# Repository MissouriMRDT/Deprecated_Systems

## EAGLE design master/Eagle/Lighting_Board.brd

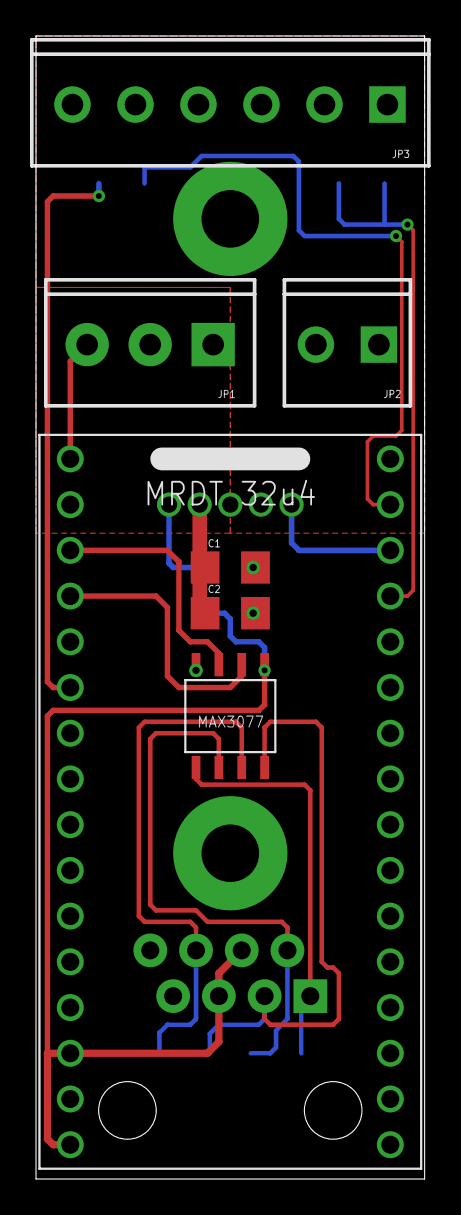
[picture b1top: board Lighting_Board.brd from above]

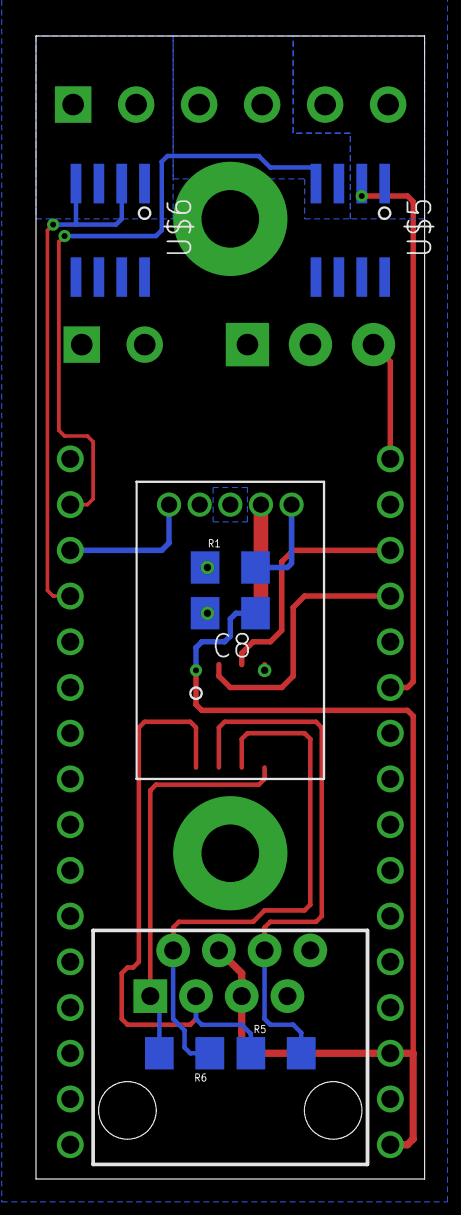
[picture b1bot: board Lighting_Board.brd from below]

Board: 2 copper layers, 21.6 x 63.5 mm, 17 parts (8 on the bottom side), 19 nets.

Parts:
C1, C2: 1206
C8: 1uF; C1206
JP1: SCREWTERMINAL-3.5MM-3
JP2: M023.5MM; SCREWTERMINAL-3.5MM-2
JP3: SCREWTERMINAL-3.5MM-6
R1: 268; 1206
R5, R6: 120 Ohm; 1206
S1, S2: STANDOFF_ELECTRICAL; STANDOFF-ELECTRICAL
U$1: OKR-T/10-W12-C
U$2: 32U4_BREAKOUT; 32U4_MCU_DIP
U$3: MAX3077; MAX3070E
U$4: RJ45-8PTH; RJ45-8
U$5, U$6: IRF8910; SO8

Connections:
+5V: C8.1, U$2.14, U$2.16, U$3.VCC, U$4.4, U$4.5
D4: JP1.3, U$2.1
D8: U$1.P$5, U$2.30
G1: U$2.6, U$5.2
G2: U$2.31, U$5.4
G3: U$2.29, U$6.2, U$6.4
GND: C1.2, C2.2, C8.2, JP1.1, JP2.1, R1.1, S1.P1, S2.P1, U$1.P$3, U$2.15, U$2.17, U$3.GND, U$4.7, U$4.8, U$5.5, U$5.6, U$5.7, U$5.8, U$6.5, U$6.6, U$6.7, U$6.8
unnamed: R1.2, U$1.P$1
unnamed: R6.2, U$3.Y, U$4.1
unnamed: R6.1, U$3.Z, U$4.2
unnamed: R5.2, U$3.B, U$4.6
unnamed: R5.1, U$3.A, U$4.3
unnamed: U$2.3, U$3.DI
RXD: U$2.4, U$3.RO
S1: JP3.5, U$5.1
S2: JP3.3, U$5.3
S3: JP3.1, U$6.1, U$6.3
VDD: C1.1, C2.1, JP1.2, U$1.P$2
VIN: JP2.2, JP3.2, JP3.4, JP3.6, U$1.P$4

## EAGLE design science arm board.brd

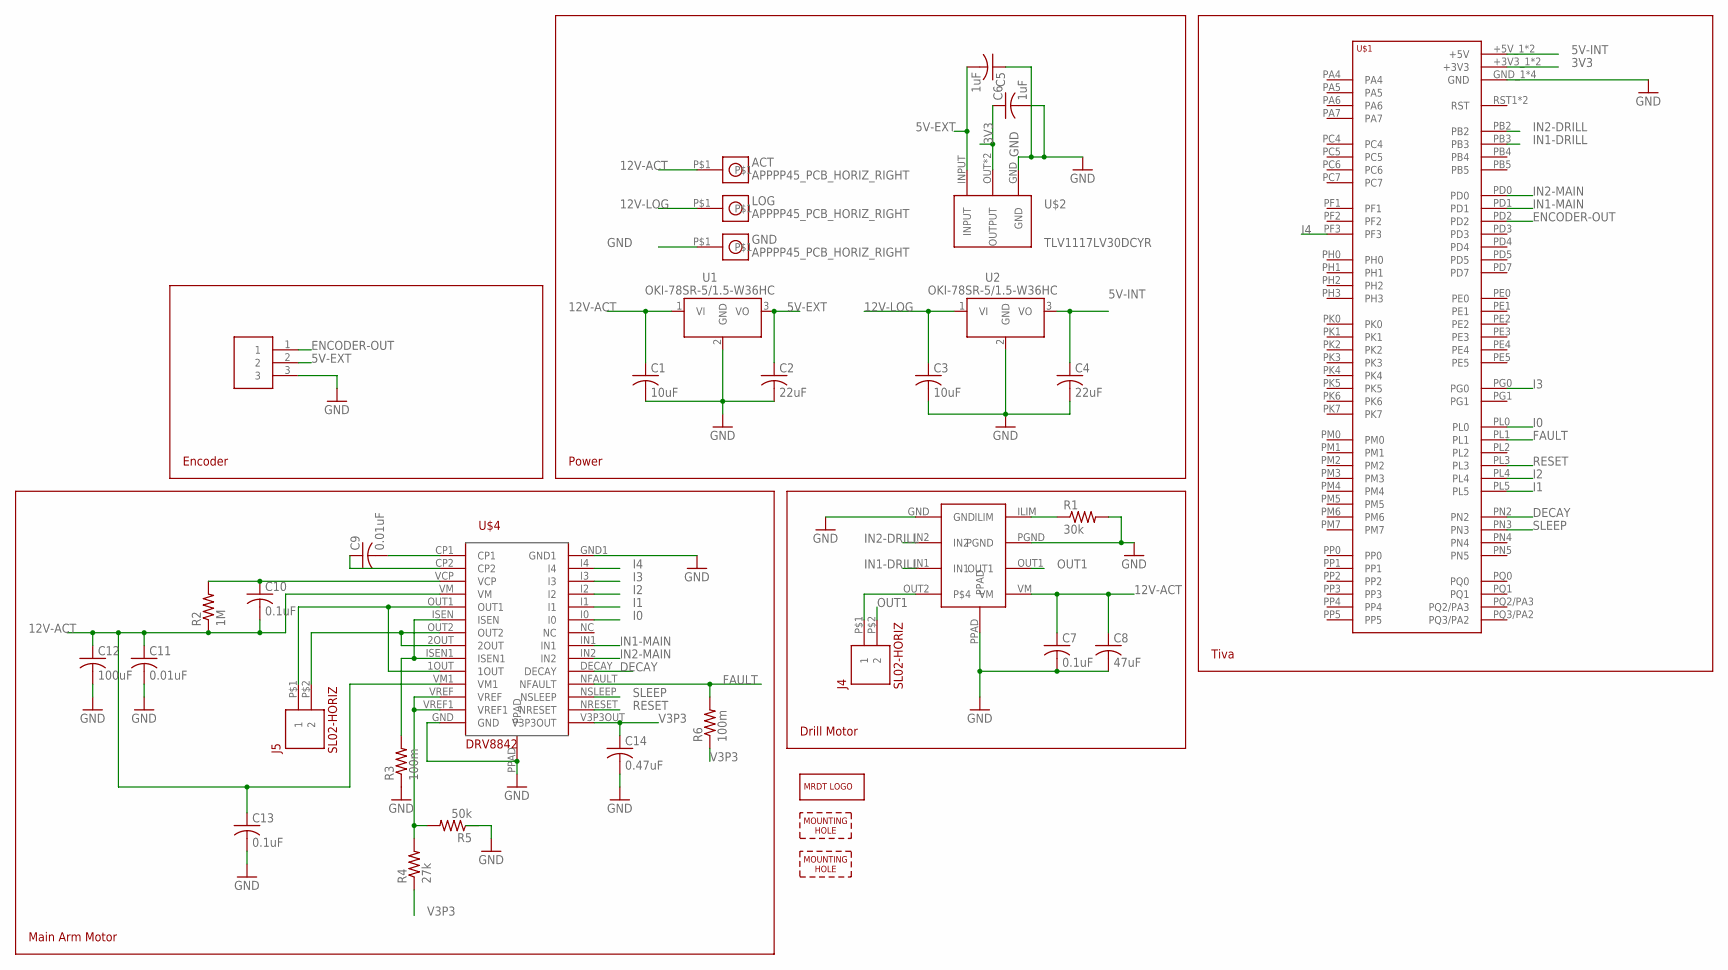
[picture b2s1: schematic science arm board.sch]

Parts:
ACT: APPPP45_PCB_HORIZ_RIGHT; APP45_PCB_HORIZ_RIGHT
C1, C3: 10uF; C1206
C2, C4: 22uF; C1206
C5, C6: 1uF; C1206
C7, C10, C13: 0.1uF; C1206
C8: 47uF; C1206
C9, C11: 0.01uF; C1206
C12: 100uF; C1206
C14: 0.47uF; C1206
GND: APPPP45_PCB_HORIZ_RIGHT; APP45_PCB_HORIZ_RIGHT
H1, H5: MOUNTING_HOLE#6; #6_SCREW
J4, J5: SL02-HORIZ; MOLEX-70551-0001
J6: SL03THROUGH_HOLE; MOLEX_SL_03_TH
LOG: APPPP45_PCB_HORIZ_RIGHT; APP45_PCB_HORIZ_RIGHT
LOGO1: MRDT_LOGO
R1: 30k; R0805
R2: 1M; R0805
R3, R6: 100m; R0805
R4: 27k; R0805
R5: 50k; R0805
U1, U2: OKI-78SR-5/1.5-W36HC; OKI-78SR_HORIZ
U$1: TIVA-1294; TIVA-C-CONNECTED
U$2: TLV1117LV30DCYR
U$3: DRV8871
U$4: DRV8842

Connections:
3V3: C6.1, U$1.+3V3_1 (+3V3), U$1.+3V3_2 (+3V3), U$2.OUT (OUTPUT), U$2.OUTPUT
5V-EXT: C2.1, C5.2, J6.2, U1.3 (VO), U$2.INPUT
5V-INT: C4.1, U2.3 (VO), U$1.+5V_1 (+5V), U$1.+5V_2 (+5V)
12V-ACT: ACT.P$1, C1.1, C7.1, C8.1, C10.2, C11.1, C12.1, C13.1, R2.1, U1.1 (VI), U$3.VM, U$4.VM, U$4.VM1
12V-LOG: C3.1, LOG.P$1, U2.1 (VI)
DECAY: U$1.PN2, U$4.DECAY
ENCODER-OUT: J6.1, U$1.PD2
FAULT: R6.2, U$1.PL1, U$4.NFAULT
GND: C1.2, C2.2, C3.2, C4.2, C5.1, C6.2, C7.2, C8.2, C11.2, C12.2, C13.2, C14.2, GND.P$1, J6.3, R1.2, R3.1, U1.2 (GND), U2.2 (GND), U$1.GND_1 (GND), U$1.GND_2 (GND), U$1.GND_3 (GND), U$1.GND_4 (GND), U$2.GND, U$3.GND, U$3.PGND, U$3.PPAD, U$4.GND, U$4.GND1, U$4.PPAD
I0: U$1.PL0, U$4.I0
I1: U$1.PL5, U$4.I1
I2: U$1.PL4, U$4.I2
I3: U$1.PG0, U$4.I3
I4: U$1.PF3, U$4.I4
IN1-DRILL: U$1.PB3, U$3.IN1
IN1-MAIN: U$1.PD1, U$4.IN1
IN2-DRILL: U$1.PB2, U$3.IN2
IN2-MAIN: U$1.PD0, U$4.IN2
unnamed: R1.1, U$3.ILIM
unnamed: J4.P$1 (1), U$3.OUT2
unnamed: R3.2, U$4.ISEN, U$4.ISEN1
unnamed: J5.P$2 (2), U$4.2OUT, U$4.OUT2
unnamed: J5.P$1 (1), U$4.1OUT, U$4.OUT1
unnamed: C9.2, U$4.CP1
unnamed: C9.1, U$4.CP2
unnamed: C10.1, R2.2, U$4.VCP
unnamed: R4.2, R5.2, U$4.VREF, U$4.VREF1
OUT1: J4.P$2 (2), U$3.OUT1
RESET: U$1.PL3, U$4.NRESET
SLEEP: U$1.PN3, U$4.NSLEEP
V3P3: C14.1, R4.1, R6.1, U$4.V3P3OUT

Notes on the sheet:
Power
Tiva
Drill Motor
Main Arm Motor
Encoder

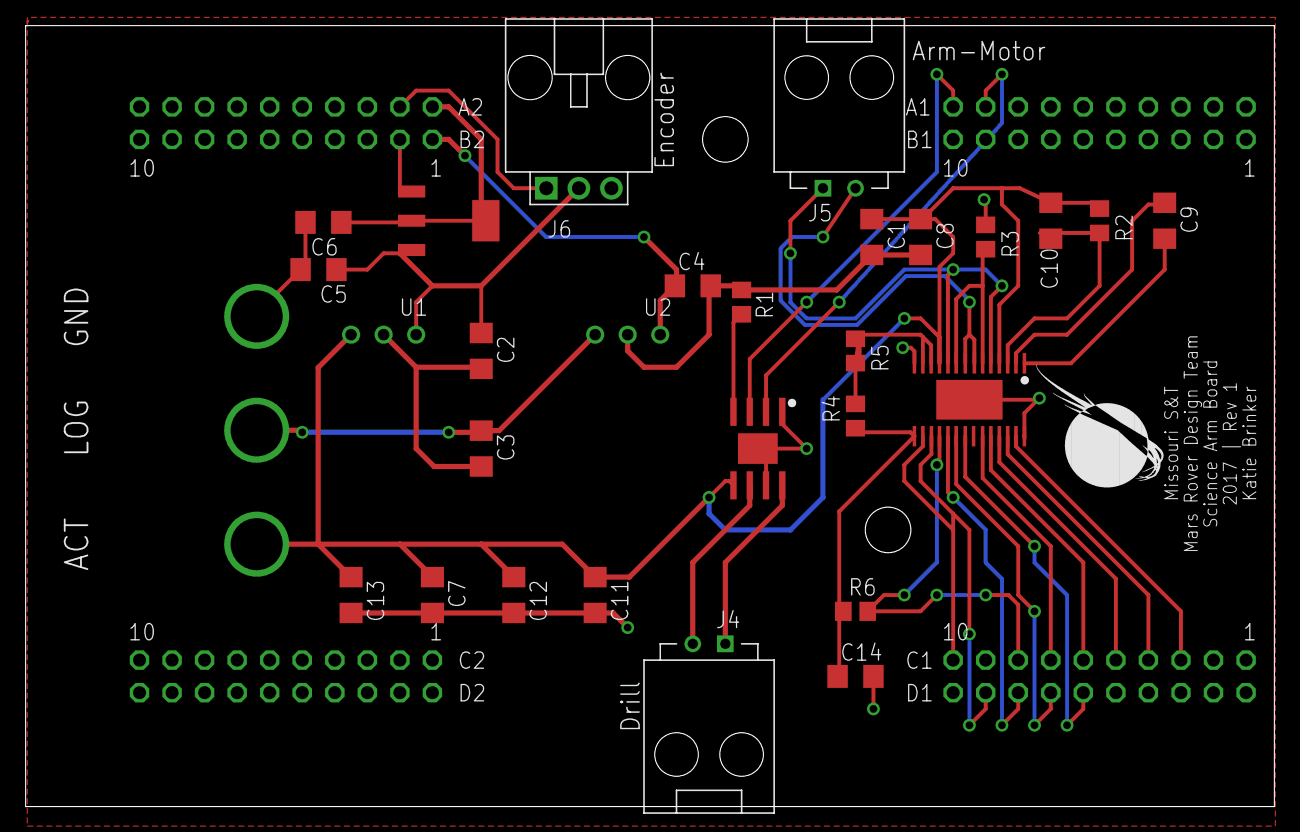
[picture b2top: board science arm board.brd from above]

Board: 2 copper layers, 97.5 x 61.0 mm, 35 parts (0 on the bottom side), 31 nets.

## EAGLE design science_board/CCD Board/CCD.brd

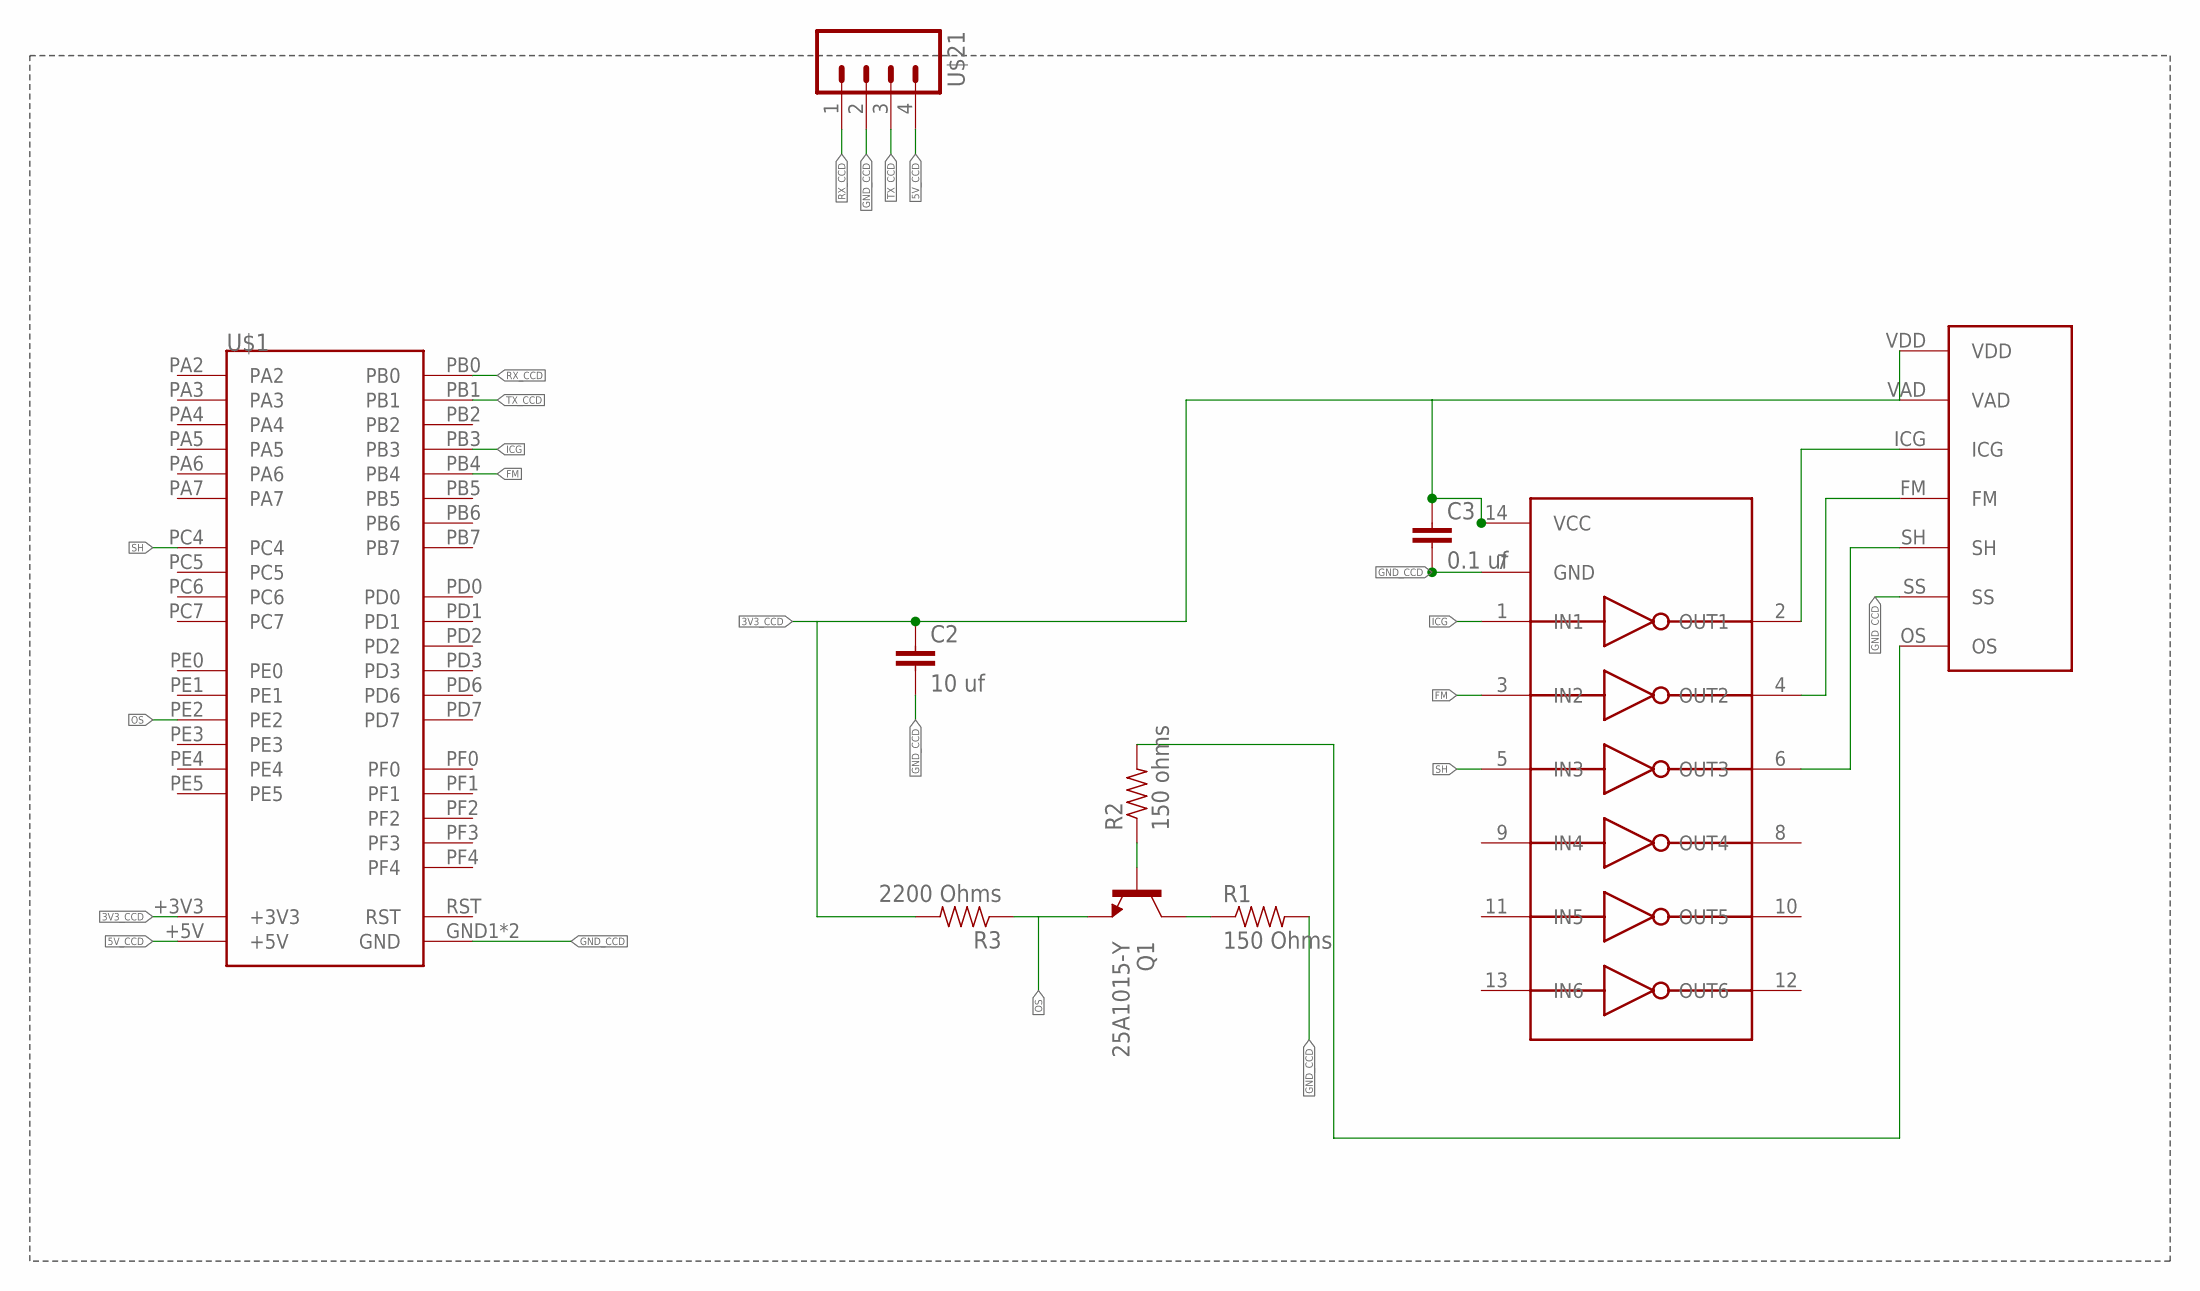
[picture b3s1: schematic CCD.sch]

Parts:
C2: 10 uf; 0603-CAP
C3: 0.1 uf; 0603-CAP
Q1: 25A1015-Y; TO-92-AMMO
R1: 150 Ohms; 0603-RES
R2: 150 ohms; 0603-RES
R3: 2200 Ohms; 0603-RES
U$1: TIVA-C
U$11: TC74HC04AP; DIP14
U$12: TCD1304DG; CCD_PACKAGE
U$21: M04; MOLEX_0436500400

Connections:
3V3_CCD: C2.1, C3.1, R3.2, U$1.+3V3, U$11.14 (VCC), U$12.VAD, U$12.VDD
5V_CCD: U$1.+5V, U$21.4
FM: U$1.PB4, U$11.3 (IN2)
GND_CCD: C2.2, C3.2, R1.2, U$1.GND1 (GND), U$1.GND2 (GND), U$11.7 (GND), U$12.SS, U$21.2
ICG: U$1.PB3, U$11.1 (IN1)
unnamed: Q1.1 (C), R1.1
unnamed: Q1.2 (B), R2.1
unnamed: U$11.2 (OUT1), U$12.ICG
unnamed: U$11.4 (OUT2), U$12.FM
unnamed: U$11.6 (OUT3), U$12.SH
unnamed: R2.2, U$12.OS
OS: Q1.3 (E), R3.1, U$1.PE2
RST: U$1.RST
RX_CCD: U$1.PB0, U$21.1
SH: U$1.PC4, U$11.5 (IN3)
TX_CCD: U$1.PB1, U$21.3

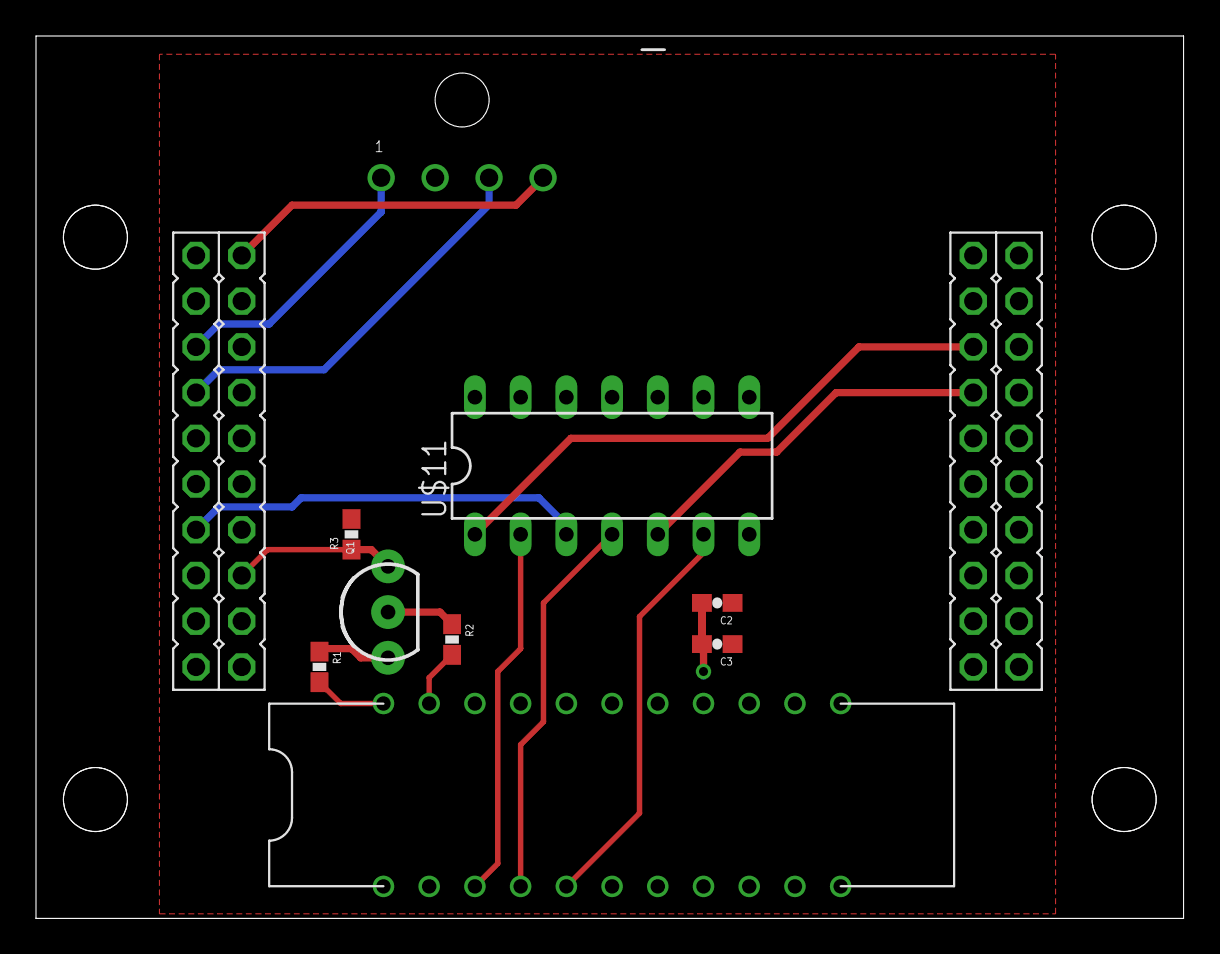
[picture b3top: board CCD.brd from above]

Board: 2 copper layers, 63.8 x 49.0 mm, 14 parts (0 on the bottom side), 15 nets.

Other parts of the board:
U$13, U$14, U$15, U$16: #6_SCREW

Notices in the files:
parts and their libraries:
SparkFun-Passives: Licensing: Creative Commons ShareAlike 4.0 International - https://creativecommons.org/licenses/by-sa/4.0
SparkFun-Aesthetics: Licensing: CC v3.0 Share-Alike You are welcome to use this library for commercial purposes.
